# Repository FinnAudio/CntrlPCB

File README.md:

These are the files for the headphones

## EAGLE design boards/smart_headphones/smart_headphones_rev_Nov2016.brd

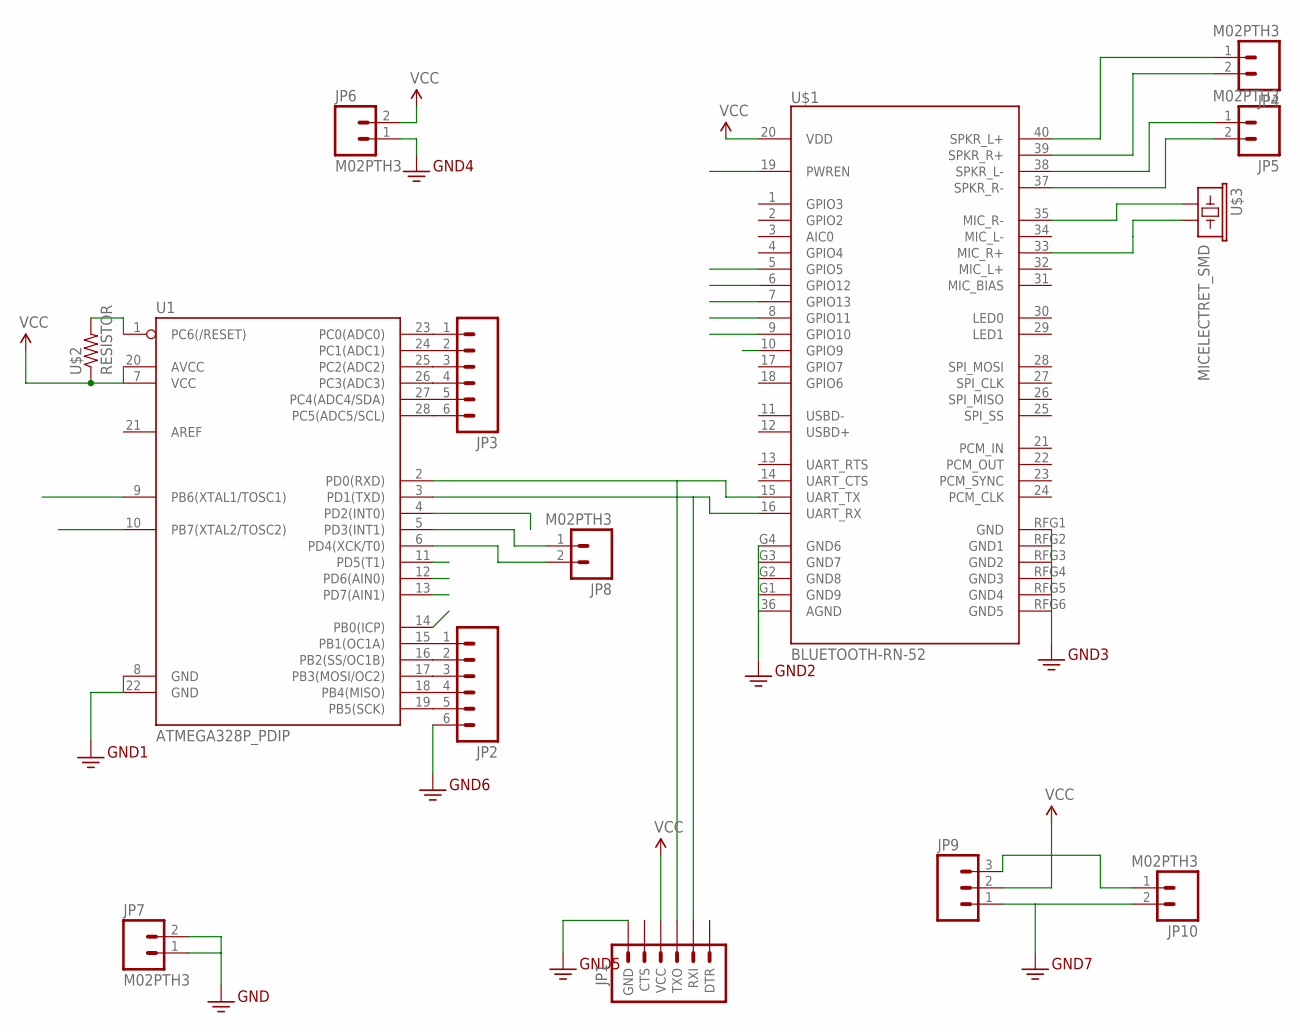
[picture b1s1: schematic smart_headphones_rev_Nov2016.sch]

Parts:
JP1: FTDI_SERIAL_PROGRAMMER_PORTLONGPADS; 1X06_LONGPADS
JP2, JP3: M06LONGPADS; 1X06_LONGPADS
JP4, JP5, JP6, JP7, JP8, JP10: M02PTH3; 1X02_LONGPADS
JP9: M03LONGPADS; 1X03_LONGPADS
U1: ATMEGA328P_PDIP; DIP28
U$1: BLUETOOTH-RN-52; RN-52
U$2: RESISTOR; 0805
U$3: MICELECTRET_SMD; MIC_ELECTRET_SMD

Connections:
GND: JP1.6 (GND), JP2.6, JP6.1, JP7.1, JP7.2, JP9.1, JP10.2, U1.8 (GND), U1.22 (GND), U$1.36 (AGND), U$1.G1 (GND9), U$1.G2 (GND8), U$1.G3 (GND7), U$1.G4 (GND6), U$1.RFG1 (GND), U$1.RFG2 (GND1), U$1.RFG3 (GND2), U$1.RFG4 (GND3), U$1.RFG5 (GND4), U$1.RFG6 (GND5)
unnamed: JP2.1, U1.15 (PB1(OC1A))
unnamed: JP2.2, U1.16 (PB2(SS/OC1B))
unnamed: JP5.2, U$1.37 (SPKR_R-)
unnamed: U1.1 (PC6(/RESET)), U$2.2
unnamed: JP1.3 (TXO), U1.2 (PD0(RXD)), U$1.15 (UART_TX)
unnamed: JP2.3, U1.17 (PB3(MOSI/OC2))
unnamed: JP4.1, U$1.40 (SPKR_L+)
unnamed: JP4.2, U$1.39 (SPKR_R+)
unnamed: JP2.4, U1.18 (PB4(MISO))
unnamed: JP1.2 (RXI), U1.3 (PD1(TXD)), U$1.16 (UART_RX)
unnamed: JP2.5, U1.19 (PB5(SCK))
unnamed: JP5.1, U$1.38 (SPKR_L-)
unnamed: U$1.35 (MIC_R-), U$3.1
unnamed: U$1.33 (MIC_R+), U$3.2
unnamed: JP8.1, U1.5 (PD3(INT1))
unnamed: JP8.2, U1.6 (PD4(XCK/T0))
unnamed: JP9.3, JP10.1
unnamed: JP3.1, U1.23 (PC0(ADC0))
unnamed: JP3.2, U1.24 (PC1(ADC1))
unnamed: JP3.3, U1.25 (PC2(ADC2))
unnamed: JP3.4, U1.26 (PC3(ADC3))
unnamed: JP3.5, U1.27 (PC4(ADC4/SDA))
unnamed: JP3.6, U1.28 (PC5(ADC5/SCL))
PB0: U1.14 (PB0(ICP)), U$1.5 (GPIO5)
PB6: U1.9 (PB6(XTAL1/TOSC1)), U$1.10 (GPIO9)
PB7: U1.10 (PB7(XTAL2/TOSC2)), U$1.9 (GPIO10)
PD5: U1.11 (PD5(T1)), U$1.8 (GPIO11)
PD6: U1.12 (PD6(AIN0)), U$1.7 (GPIO13)
PD7: U1.13 (PD7(AIN1)), U$1.6 (GPIO12)
PWREN: U1.4 (PD2(INT0)), U$1.19 (PWREN)
VCC: JP1.4 (VCC), JP6.2, JP9.2, U1.7 (VCC), U1.20 (AVCC), U$1.20 (VDD), U$2.1

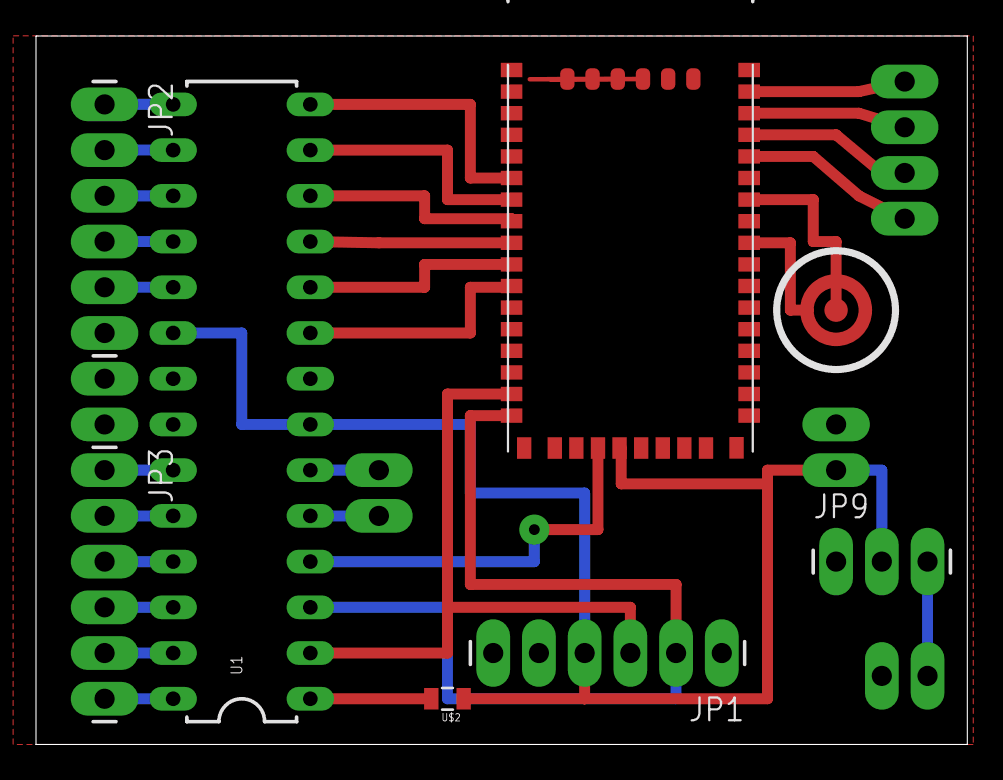
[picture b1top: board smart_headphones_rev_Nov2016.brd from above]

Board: 2 copper layers, 51.7 x 39.4 mm, 14 parts (0 on the bottom side), 32 nets.

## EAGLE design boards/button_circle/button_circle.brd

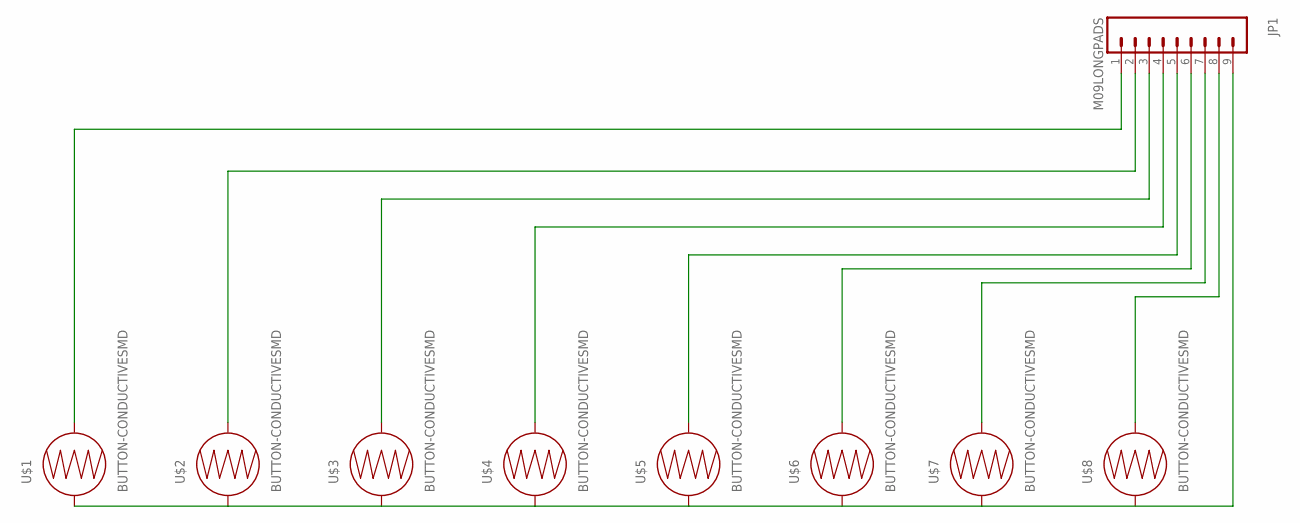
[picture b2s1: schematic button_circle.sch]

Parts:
JP1: M09LONGPADS; 1X09_LONGPADS
U$1, U$2, U$3, U$4, U$5, U$6, U$7, U$8: BUTTON-CONDUCTIVESMD; BUTTON-CONDUCTIVE

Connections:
GND: JP1.9, U$1.1, U$2.1, U$3.1, U$4.1, U$5.1, U$7.1
unnamed: JP1.8, U$8.2
unnamed: JP1.7, U$7.2
unnamed: JP1.6, U$6.2
unnamed: JP1.5, U$5.2
unnamed: JP1.4, U$4.2
unnamed: JP1.3, U$3.2
unnamed: JP1.2, U$2.2
unnamed: JP1.1, U$1.2

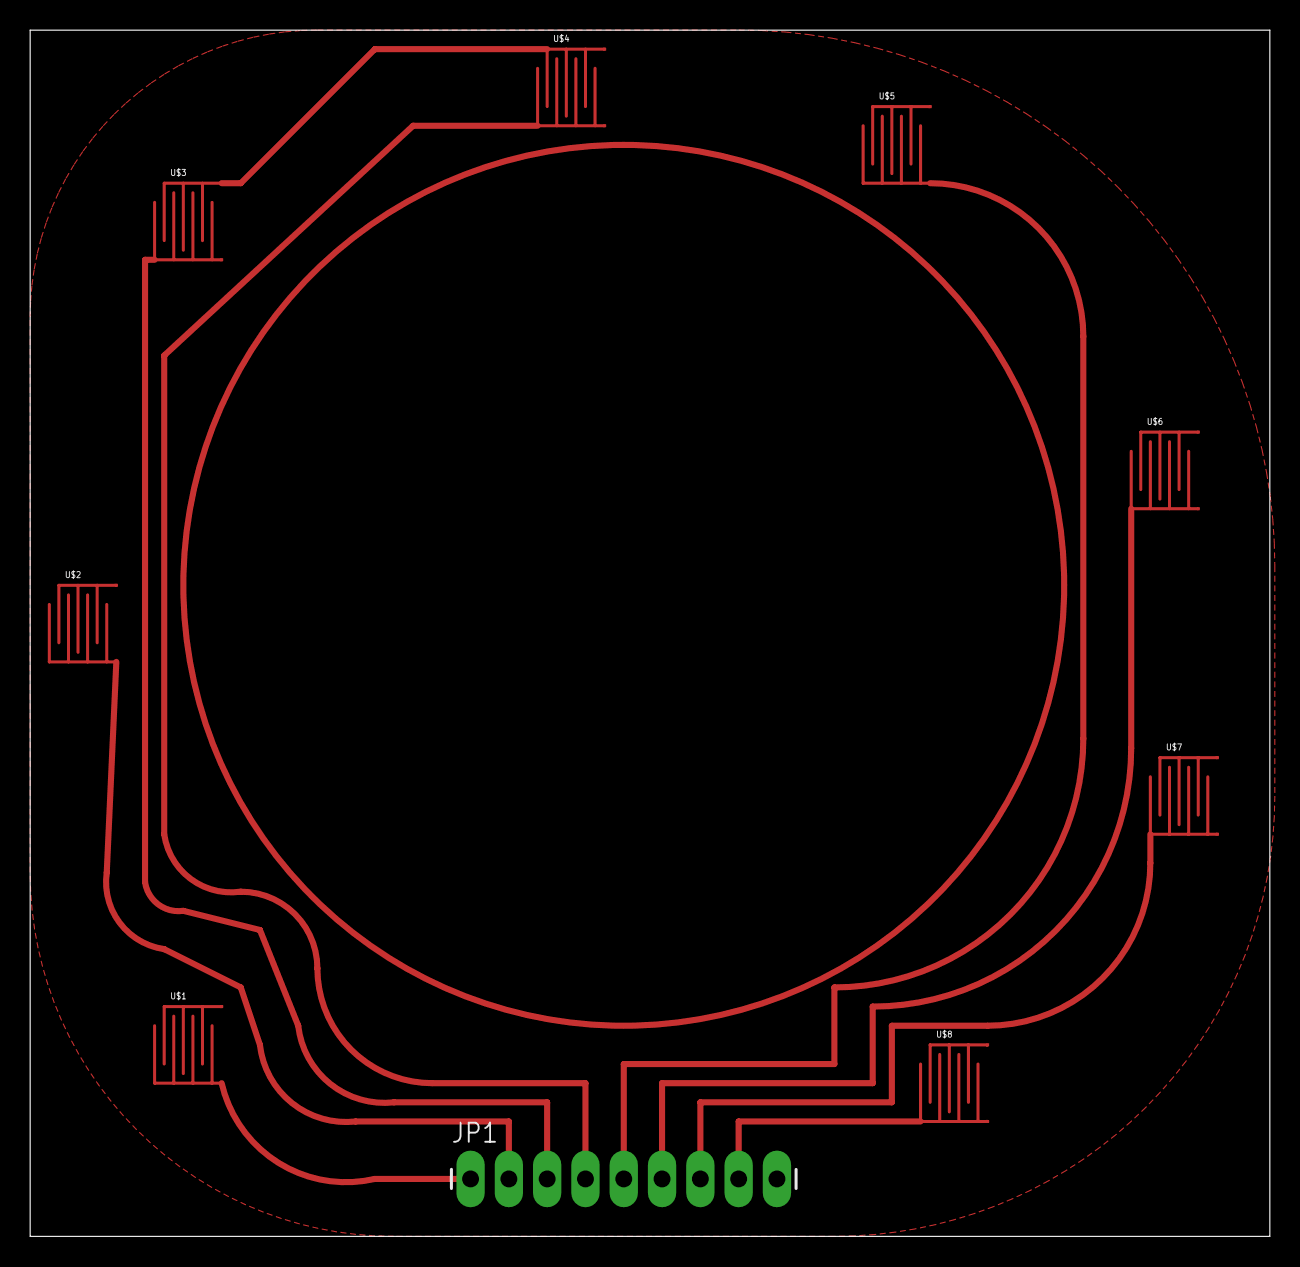
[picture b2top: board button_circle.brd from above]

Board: 2 copper layers, 82.2 x 80.0 mm, 9 parts (0 on the bottom side), 9 nets.

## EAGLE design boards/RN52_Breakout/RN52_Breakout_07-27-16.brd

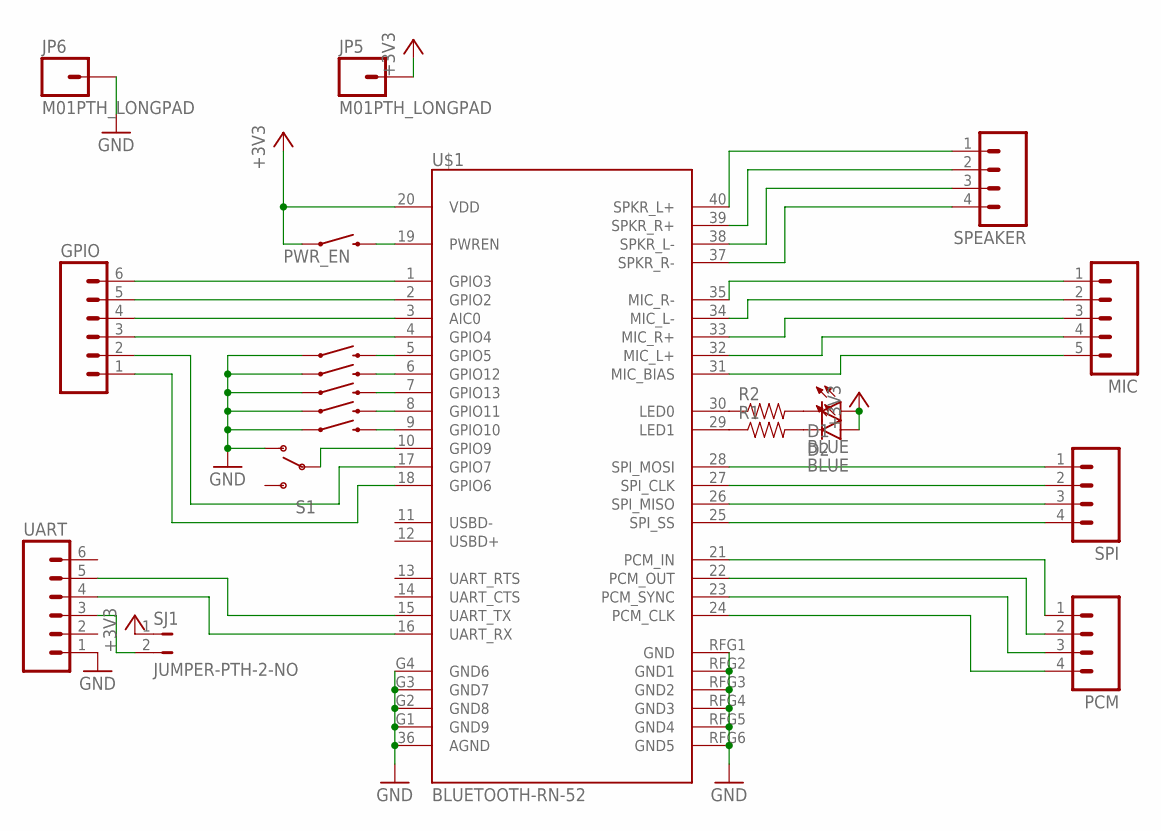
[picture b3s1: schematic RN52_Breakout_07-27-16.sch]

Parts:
D1, D2: BLUE; LED-1206
GPIO: M06LONGPADS; 1X06_LONGPADS
JP5, JP6: M01PTH_LONGPAD; 1X01_LONGPAD
MIC: M05PTH_LONGPADS; 1X05_LONGPADS
PCM: M04LONGPADS; 1X04_LONGPADS
PWR_EN, PWR_EN1, PWR_EN2, PWR_EN3, PWR_EN4, PWR_EN5: SWITCH-MOMENTARY-2PTH; TACTILE-PTH
R1, R2: 3.3MOHM-1/10W-1%(0603); 0603-RES
S1: SWITCH-SPDTPTH; SWITCH-SPDT
SJ1: JUMPER-PTH-2-NO; PTH-JUMPER-2-NO_NO_SILK
SPEAKER: M04LONGPADS; 1X04_LONGPADS
SPI: M04LONGPADS; 1X04_LONGPADS
U$1: BLUETOOTH-RN-52; RN-52
UART: M06LONGPADS; 1X06_LONGPADS

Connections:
+3V3: D1.A, D2.A, JP5.1, PWR_EN.1, SJ1.1, U$1.20 (VDD)
GND: JP6.1, PWR_EN1.1, PWR_EN2.1, PWR_EN3.1, PWR_EN4.1, PWR_EN5.1, S1.1 (O), U$1.36 (AGND), U$1.G1 (GND9), U$1.G2 (GND8), U$1.G3 (GND7), U$1.G4 (GND6), U$1.RFG1 (GND), U$1.RFG2 (GND1), U$1.RFG3 (GND2), U$1.RFG4 (GND3), U$1.RFG5 (GND4), U$1.RFG6 (GND5), UART.1
unnamed: PWR_EN1.3 (2), U$1.5 (GPIO5)
unnamed: PWR_EN.3 (2), U$1.19 (PWREN)
unnamed: PWR_EN2.3 (2), U$1.6 (GPIO12)
unnamed: PWR_EN3.3 (2), U$1.7 (GPIO13)
unnamed: PWR_EN4.3 (2), U$1.8 (GPIO11)
unnamed: PWR_EN5.3 (2), U$1.9 (GPIO10)
unnamed: S1.2, U$1.10 (GPIO9)
unnamed: R1.1, U$1.29 (LED1)
unnamed: R2.1, U$1.30 (LED0)
unnamed: D1.C, R2.2
unnamed: D2.C, R1.2
unnamed: SPEAKER.1, U$1.40 (SPKR_L+)
unnamed: SPEAKER.2, U$1.39 (SPKR_R+)
unnamed: SPEAKER.3, U$1.38 (SPKR_L-)
unnamed: SPEAKER.4, U$1.37 (SPKR_R-)
unnamed: MIC.1, U$1.35 (MIC_R-)
unnamed: MIC.2, U$1.34 (MIC_L-)
unnamed: MIC.3, U$1.33 (MIC_R+)
unnamed: MIC.4, U$1.32 (MIC_L+)
unnamed: MIC.5, U$1.31 (MIC_BIAS)
unnamed: SPI.1, U$1.28 (SPI_MOSI)
unnamed: SPI.2, U$1.27 (SPI_CLK)
unnamed: SPI.3, U$1.26 (SPI_MISO)
unnamed: SPI.4, U$1.25 (SPI_SS)
unnamed: SJ1.2, UART.3
unnamed: U$1.16 (UART_RX), UART.4
unnamed: U$1.15 (UART_TX), UART.5
unnamed: PCM.1, U$1.21 (PCM_IN)
unnamed: PCM.2, U$1.22 (PCM_OUT)
unnamed: PCM.3, U$1.23 (PCM_SYNC)
unnamed: PCM.4, U$1.24 (PCM_CLK)
unnamed: GPIO.6, U$1.1 (GPIO3)
unnamed: GPIO.5, U$1.2 (GPIO2)
unnamed: GPIO.4, U$1.3 (AIC0)
unnamed: GPIO.3, U$1.4 (GPIO4)
unnamed: GPIO.2, U$1.17 (GPIO7)
unnamed: GPIO.1, U$1.18 (GPIO6)

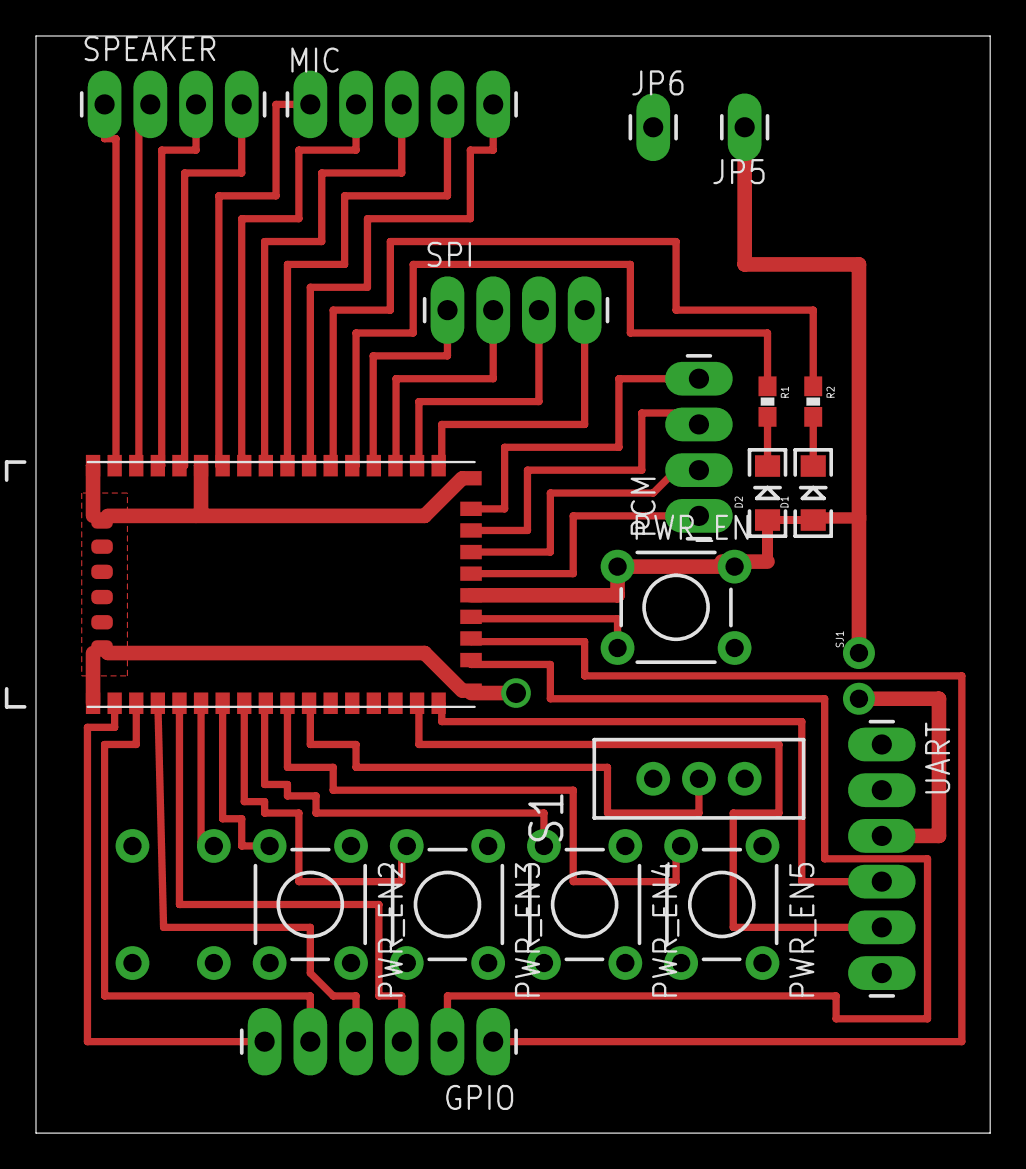
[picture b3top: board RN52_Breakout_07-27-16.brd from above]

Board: 2 copper layers, 53.0 x 61.0 mm, 21 parts (1 on the bottom side), 39 nets.

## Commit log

2016-10-23 Initial Commit. Library working
2016-11-06 Finished first AVR driven bluetooth smart headphone board
2016-11-06 Updated Eagle version?
2016-11-07 Fixed bug (two control signals connected)

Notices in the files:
parts and their libraries:
SparkFun-LED: Licensing: Creative Commons ShareAlike 4.0 International - https://creativecommons.org/licenses/by-sa/4.0
Finn-lbr-rev1: Released under the Creative Commons
Finn-lbr-rev1: https://creativecommons.org/licenses/by-sa/4.0
